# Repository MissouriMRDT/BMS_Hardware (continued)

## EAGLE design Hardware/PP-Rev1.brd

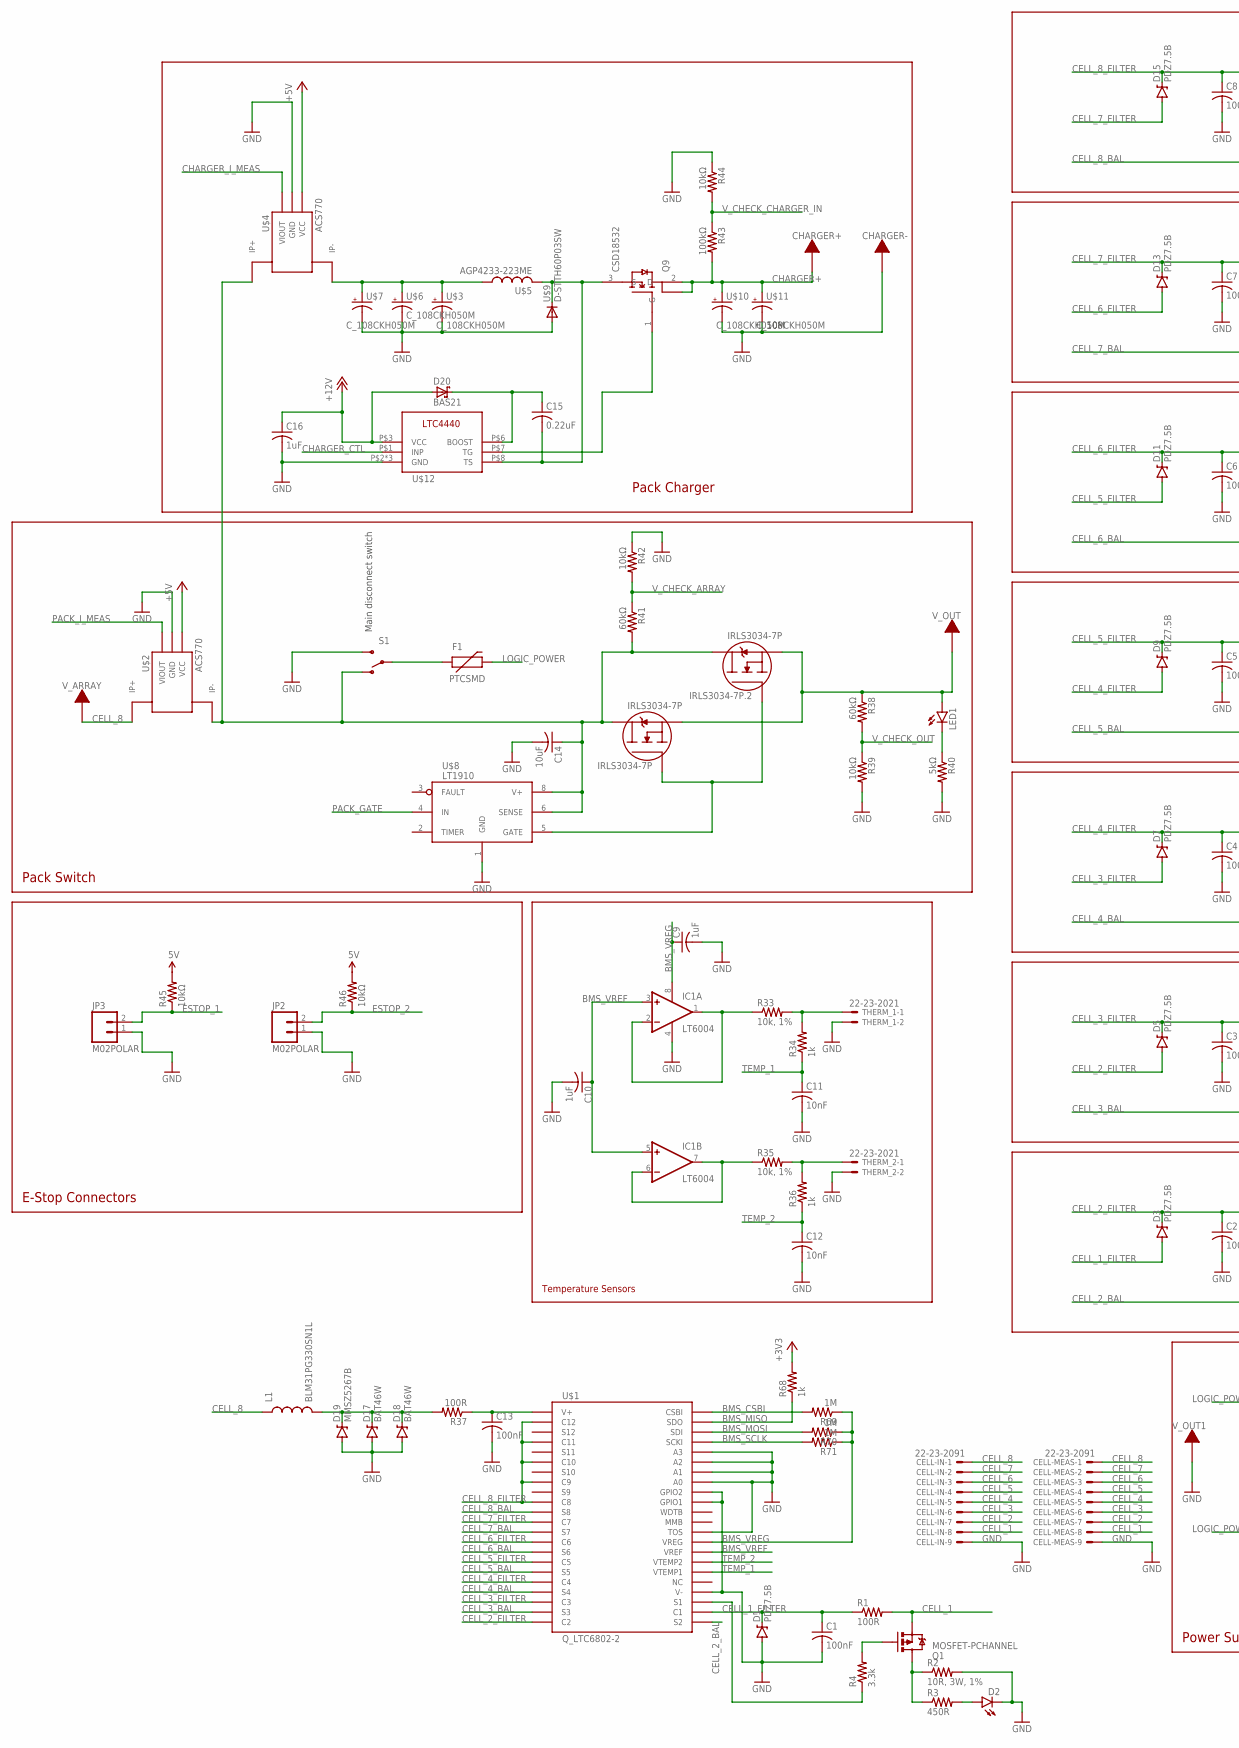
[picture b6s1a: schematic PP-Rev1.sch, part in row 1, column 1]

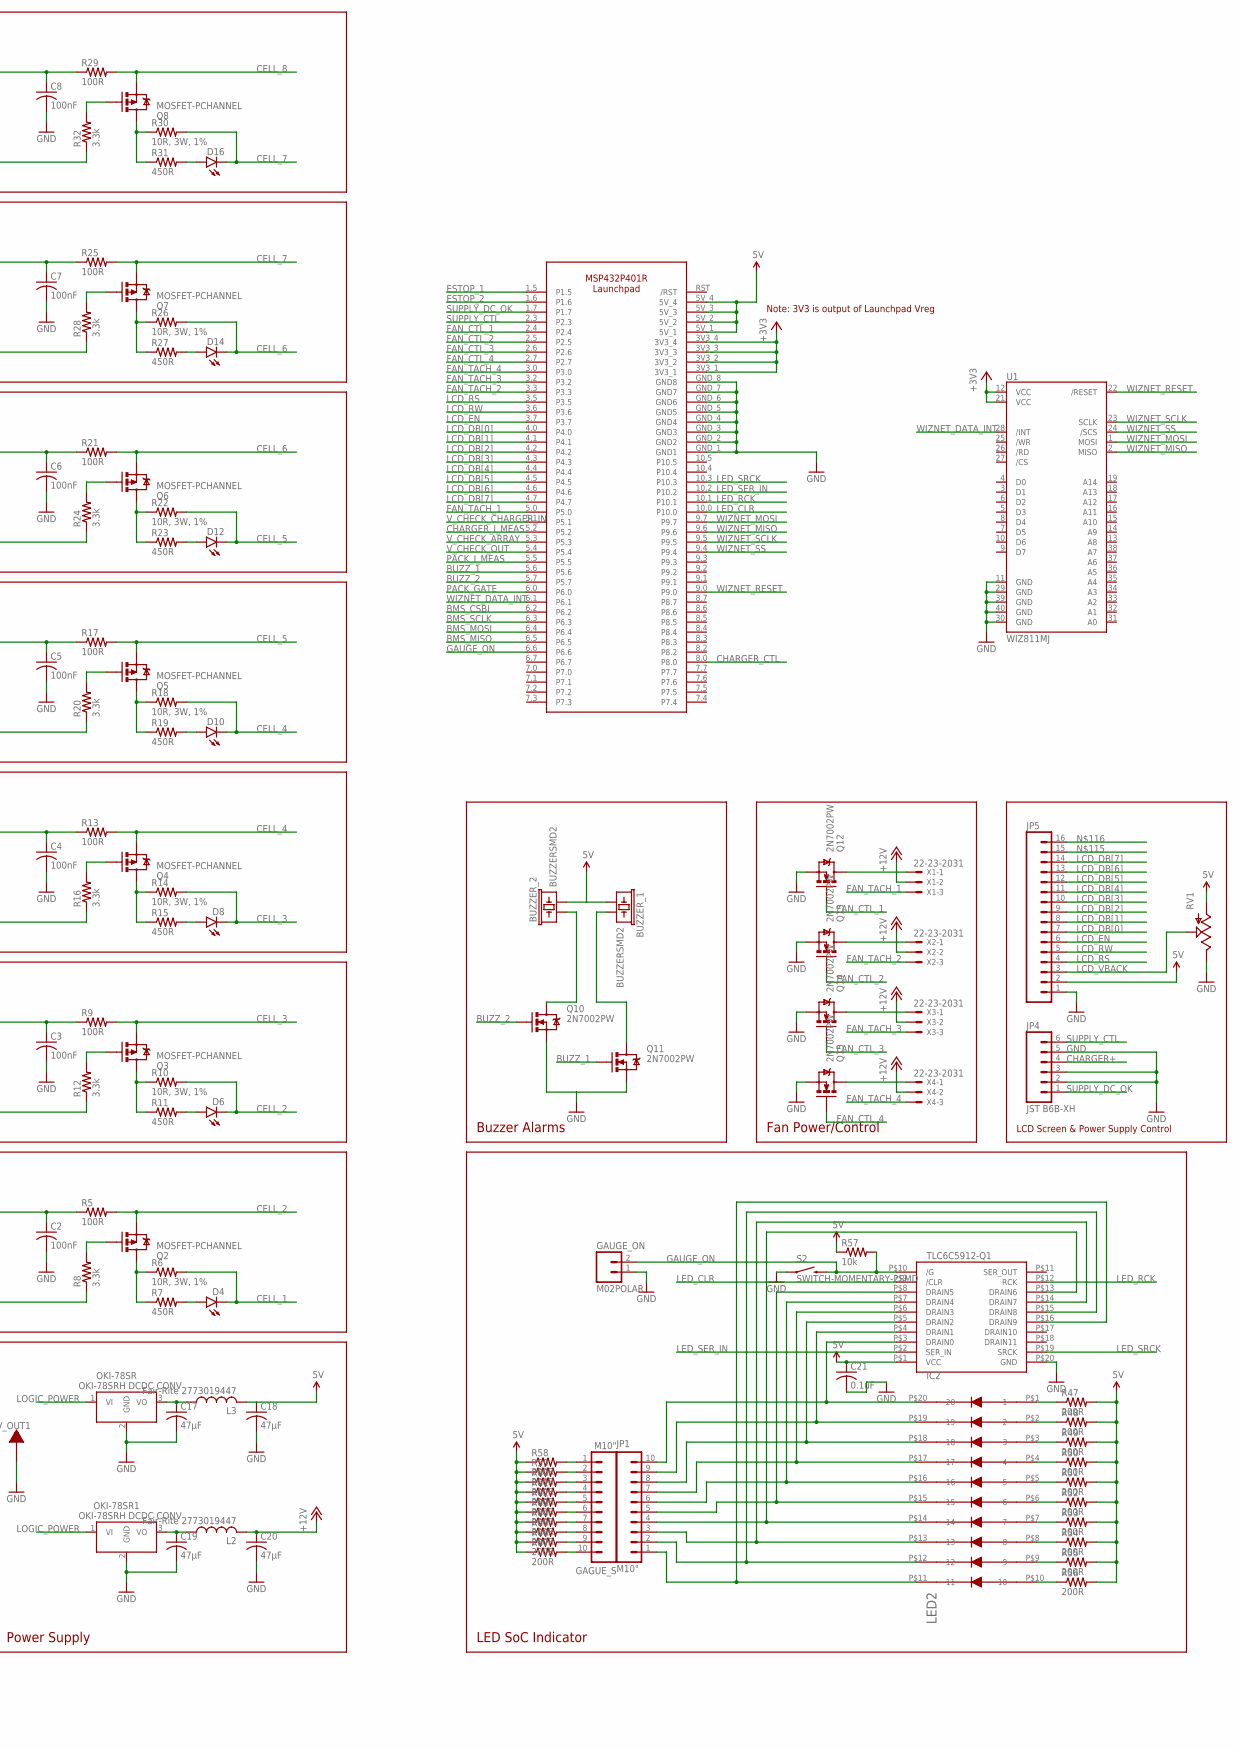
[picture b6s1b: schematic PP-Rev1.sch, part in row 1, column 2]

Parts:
BUZZER_1, BUZZER_2: BUZZERSMD2; BUZZER-CCV
C1, C2, C3, C4, C5, C6, C7, C8, C13: 100nF; C1206
C9, C10, C16: 1uF; C1206
C11, C12: 10nF; C1206
C14: 10uF; C1206
C15: 0.22uF; C1206
C17, C18, C19, C20: 47µF; C1206
C21: 0.1uF; C1206
CELL-IN: 22-23-2091
CELL-MEAS: 22-23-2091
CHARGER+: TERMINAL_HOLE; LARGE_TERMINAL_HOLE
CHARGER-: TERMINAL_HOLE; LARGE_TERMINAL_HOLE
D1, D3, D5, D7, D9, D11, D13, D15: PDZ7.5B; SOD-323
D2, D4, D6, D8, D10, D12, D14, D16: LED1206; LED-1206
D17, D18: BAT46W; SOD-123
D19: MMSZ5267B; SOD-123
D20: BAS21; SOT23
F1: PTCSMD; PTC-1206
GAGUE_S: M10"; 1X10
GAUGE_ON: M02POLAR; MOLEX-1X2
IC1: LT6004; MSOP08
IC2: TLC6C5912-Q1; SOIC-20
IRLS3034-7P, IRLS3034-7P.2: IRLS3034-7P; D2PAK-7
JP1: M10"; 1X10
JP2, JP3: M02POLAR; MOLEX-1X2
JP4: JST B6B-XH; MOLEX-1X6
JP5: M16LONGPADS; 1X16_LONGPADS
L1: BLM31PG330SN1L; 1210
L2, L3: Fair-Rite 2773019447; L8530M
LED1: LED1206; LED-1206
LED2: LED-DC7G3HWA; LED-10
OKI-78SR: Q_OKI-78SR5; OKI-78SRH
OKI-78SR1: Q_OKI-78SR12; OKI-78SRH
Q1, Q2, Q3, Q4, Q5, Q6, Q7, Q8: MOSFET-PCHANNEL; SOT23-3
Q9: CSD18532; TO-220-FLAT
Q10, Q11, Q12, Q13, Q14, Q15: 2N7002PW; SOT323
R1, R5, R9, R13, R17, R21, R25, R29, R37: 100R; R1206
R2, R6, R10, R14, R18, R22, R26, R30: 10R, 3W, 1%; AXIAL-0.6
R3, R7, R11, R15, R19, R23, R27, R31: 450R; 1206
R4, R8, R12, R16, R20, R24, R28, R32: 3.3k; 1206
R33, R35: 10k, 1%; R1206
R34, R36, R68: 1k; R1206
R38, R41: 60kΩ; R1206
R39, R42, R44, R45, R46: 10kΩ; R1206
R40: 5kΩ; R1206
R43: 100kΩ; R1206
R47, R48, R49, R50, R51, R52, R53, R54, R55, R56, R58, R59, R60, R61, R62, R63, R64, R65, R66, R67: 200R; R1206
R57: 10k; R1206
R69, R70, R71: 1M; R1206
RV1: POTTRIM; TRIM_POT
S1: SWITCH-SPDTPTH; SWITCH-SPDT
S2: SWITCH-MOMENTARY-2SMD; TACTILE-SWITCH-SMD
THERM_1, THERM_2: 22-23-2021
U1: WIZ811MJ
U$1: Q_LTC6802-2; SSOP44
U$2, U$4: ACS770; PFF_LEADFORM
U$3, U$6, U$7, U$10, U$11: C_108CKH050M; C_16MM
U$5: AGP4233-223ME; AGP4233
U$8: LT1910; SO8
U$9: D-STTH60P03SW; TO-247-VERT
U$12: LTC4440; MS8E
U$13: MSP432P401R-LAUNCHPAD
V_ARRAY: TERMINAL_HOLE; LARGE_TERMINAL_HOLE
V_OUT, V_OUT1: TERMINAL_HOLE; LARGE_TERMINAL_HOLE
X1, X2, X3, X4: 22-23-2031

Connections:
5V: BUZZER_1.+ (1), BUZZER_2.- (2), C18.1, C21.1, IC2.P$1 (VCC), JP5.2, L3.2, R45.2, R46.2, R47.2, R48.2, R49.2, R50.2, R51.2, R52.2, R53.2, R54.2, R55.2, R56.2, R57.1, R58.1, R59.1, R60.1, R61.1, R62.1, R63.1, R64.1, R65.1, R66.1, R67.1, RV1.3 (A), U$13.5V_1, U$13.5V_2, U$13.5V_3, U$13.5V_4
+3V3: R68.2, U1.12 (VCC), U1.21 (VCC), U$13.3V3_1, U$13.3V3_2, U$13.3V3_3, U$13.3V3_4
+5V: U$2.1 (VCC), U$4.1 (VCC)
+12V: C16.1, C20.1, D20.1 (A), L2.2, U$12.P$3 (VCC), X1.2, X2.2, X3.2, X4.2
BMS_CSBI: R69.2, U$1.44 (CSBI), U$13.6.2
BMS_MISO: R68.1, U$1.43 (SDO), U$13.6.5
BMS_MOSI: R70.2, U$1.42 (SDI), U$13.6.4
BMS_SCLK: R71.2, U$1.41 (SCKI), U$13.6.3
BMS_VREF: C10.1, IC1.3 (+IN), IC1.5 (+IN), U$1.30 (VREF)
BMS_VREG: C9.1, IC1.8 (V+), R69.1, R70.1, R71.1, U$1.31 (VREG)
BUZZ_1: Q11.1 (G), U$13.5.6
BUZZ_2: Q10.1 (G), U$13.5.7
CELL_1: CELL-IN.8, CELL-MEAS.8, D4.C, Q1.2 (S), R1.2, R6.P$2 (2)
CELL_1_BAL: R4.1, U$1.25 (S1)
CELL_1_FILTER: C1.1, D1.C, D3.A, R1.1, U$1.24 (C1)
CELL_2: CELL-IN.7, CELL-MEAS.7, D6.C, Q2.2 (S), R5.2, R10.P$2 (2)
CELL_2_BAL: R8.1, U$1.23 (S2)
CELL_2_FILTER: C2.1, D3.C, D5.A, R5.1, U$1.22 (C2)
CELL_3: CELL-IN.6, CELL-MEAS.6, D8.C, Q3.2 (S), R9.2, R14.P$2 (2)
CELL_3_BAL: R12.1, U$1.21 (S3)
CELL_3_FILTER: C3.1, D5.C, D7.A, R9.1, U$1.20 (C3)
CELL_4: CELL-IN.5, CELL-MEAS.5, D10.C, Q4.2 (S), R13.2, R18.P$2 (2)
CELL_4_BAL: R16.1, U$1.19 (S4)
CELL_4_FILTER: C4.1, D7.C, D9.A, R13.1, U$1.18 (C4)
CELL_5: CELL-IN.4, CELL-MEAS.4, D12.C, Q5.2 (S), R17.2, R22.P$2 (2)
CELL_5_BAL: R20.1, U$1.17 (S5)
CELL_5_FILTER: C5.1, D9.C, D11.A, R17.1, U$1.16 (C5)
CELL_6: CELL-IN.3, CELL-MEAS.3, D14.C, Q6.2 (S), R21.2, R26.P$2 (2)
CELL_6_BAL: R24.1, U$1.15 (S6)
CELL_6_FILTER: C6.1, D11.C, D13.A, R21.1, U$1.14 (C6)
CELL_7: CELL-IN.2, CELL-MEAS.2, D16.C, Q7.2 (S), R25.2, R30.P$2 (2)
CELL_7_BAL: R28.1, U$1.13 (S7)
CELL_7_FILTER: C7.1, D13.C, D15.A, R25.1, U$1.12 (C7)
CELL_8: CELL-IN.1, CELL-MEAS.1, L1.1, Q8.2 (S), R29.2, U$2.4_1 (IP+), U$2.4_2 (IP+), U$2.4_3 (IP+), U$2.4_4 (IP+), U$2.4_5 (IP+), U$2.4_6 (IP+), U$2.4_7 (IP+), U$2.4_8 (IP+), U$2.4_9 (IP+), U$2.4_10 (IP+), U$2.4_11 (IP+), U$2.4_12 (IP+), U$2.4_13 (IP+), U$2.4_14 (IP+), U$2.4_15 (IP+), U$2.4_16 (IP+), U$2.4_B (IP+), U$2.4_T (IP+), V_ARRAY.P$1
CELL_8_BAL: R32.1, U$1.11 (S8)
CELL_8_FILTER: C8.1, D15.C, R29.1, U$1.2 (C12), U$1.4 (C11), U$1.6 (C10), U$1.8 (C9), U$1.10 (C8)
CHARGER+: CHARGER+.P$1, JP4.4, Q9.2 (D), Q9.4, R43.2, U$10.+, U$11.+
CHARGER_CTL: U$12.P$1 (INP), U$13.8.0
CHARGER_I_MEAS: U$4.3 (VIOUT), U$13.5.2
ESTOP_1: JP3.2, R45.1, U$13.1.5
ESTOP_2: JP2.2, R46.1, U$13.1.6
FAN_CTL_1: Q12.1 (G), U$13.2.4
FAN_CTL_2: Q13.1 (G), U$13.2.5
FAN_CTL_3: Q14.1 (G), U$13.2.6
FAN_CTL_4: Q15.1 (G), U$13.2.7
FAN_TACH_1: U$13.5.0, X1.3
FAN_TACH_2: U$13.3.3, X2.3
FAN_TACH_3: U$13.3.2, X3.3
FAN_TACH_4: U$13.3.0, X4.3
GAUGE_D: IC2.P$6 (DRAIN3), JP1.7, LED2.P$17 (17)
GAUGE_ON: GAUGE_ON.2, IC2.P$10 (/G), R57.2, S2.3 (2), U$13.6.6
GND: C1.2, C2.2, C3.2, C4.2, C5.2, C6.2, C7.2, C8.2, C9.2, C10.2, C11.2, C12.2, C13.2, C14.2, C16.2, C17.2, C18.2, C19.2, C20.2, C21.2, CELL-IN.9, CELL-MEAS.9, CHARGER-.P$1, D1.A, D2.C, D17.A, D18.A, D19.A, GAUGE_ON.1, IC1.4 (V-), IC2.P$20 (GND), JP2.1, JP3.1, JP4.2, JP4.3, JP4.5, JP5.1, OKI-78SR.2 (GND), OKI-78SR1.2 (GND), Q10.2 (S), Q11.2 (S), Q12.2 (S), Q13.2 (S), Q14.2 (S), Q15.2 (S), R2.P$2 (2), R39.2, R40.2, R42.1, R44.1, RV1.2 (E), S1.3 (S), S2.1, THERM_1.2, THERM_2.2, U1.11 (GND), U1.29 (GND), U1.30 (GND), U1.39 (GND), U1.40 (GND), U$1.26 (V-), U$1.32 (TOS), U$1.35 (GPIO1), U$1.36 (GPIO2), U$1.37 (A0), U$1.38 (A1), U$1.39 (A2), U$1.40 (A3), U$2.2 (GND), U$3.GND (-), U$4.2 (GND), U$6.GND (-), U$7.GND (-), U$8.1 (GND), U$9.P$1 (A), U$9.P$3 (A), U$10.GND (-), U$11.GND (-), U$12.P$2 (GND), U$12.P$4 (GND), U$12.P$9 (GND), U$13.GND_1 (GND1), U$13.GND_2 (GND2), U$13.GND_3 (GND3), U$13.GND_4 (GND4), U$13.GND_5 (GND5), U$13.GND_6 (GND6), U$13.GND_7 (GND7), U$13.GND_8 (GND8), V_OUT1.P$1
LCD_DB[0]: JP5.7, U$13.4.0
LCD_DB[1]: JP5.8, U$13.4.1
LCD_DB[2]: JP5.9, U$13.4.2
LCD_DB[3]: JP5.10, U$13.4.3
LCD_DB[4]: JP5.11, U$13.4.4
LCD_DB[5]: JP5.12, U$13.4.5
LCD_DB[6]: JP5.13, U$13.4.6
LCD_DB[7]: JP5.14, U$13.4.7
LCD_EN: JP5.6, U$13.3.7
LCD_RS: JP5.4, U$13.3.5
LCD_RW: JP5.5, U$13.3.6
LCD_VBACK: JP5.3, RV1.1 (S)
LED_CLR: IC2.P$9 (/CLR), U$13.10.0
LED_RCK: IC2.P$12 (RCK), U$13.10.1
LED_SER_IN: IC2.P$2 (SER_IN), U$13.10.2
LED_SRCK: IC2.P$19 (SRCK), U$13.10.3
LOGIC_POWER: F1.2, OKI-78SR.1 (VI), OKI-78SR1.1 (VI)
unnamed: Q3.3 (D), R10.P$1 (1), R11.1
unnamed: Q1.3 (D), R2.P$1 (1), R3.1
unnamed: D2.A, R3.2
unnamed: D6.A, R11.2
unnamed: Q1.1 (G), R4.2
unnamed: Q3.1 (G), R12.2
unnamed: Q2.3 (D), R6.P$1 (1), R7.1
unnamed: D4.A, R7.2
unnamed: Q2.1 (G), R8.2
unnamed: Q4.3 (D), R14.P$1 (1), R15.1
unnamed: D8.A, R15.2
unnamed: Q4.1 (G), R16.2
unnamed: Q5.3 (D), R18.P$1 (1), R19.1
unnamed: D10.A, R19.2
unnamed: Q5.1 (G), R20.2
unnamed: Q6.3 (D), R22.P$1 (1), R23.1
unnamed: D12.A, R23.2
unnamed: Q6.1 (G), R24.2
unnamed: Q7.3 (D), R26.P$1 (1), R27.1
unnamed: D14.A, R27.2
unnamed: Q7.1 (G), R28.2
unnamed: Q8.3 (D), R30.P$1 (1), R31.1
unnamed: D16.A, R31.2
unnamed: Q8.1 (G), R32.2
unnamed: IC1.1 (OUT), IC1.2 (-IN), R33.1
unnamed: D17.C, D18.C, D19.C, L1.2, R37.2
unnamed: IC1.6 (-IN), IC1.7 (OUT), R35.1
unnamed: U$3.+, U$4.5_1 (IP-), U$4.5_2 (IP-), U$4.5_3 (IP-), U$4.5_4 (IP-), U$4.5_5 (IP-), U$4.5_6 (IP-), U$4.5_7 (IP-), U$4.5_8 (IP-), U$4.5_9 (IP-), U$4.5_10 (IP-), U$4.5_11 (IP-), U$4.5_12 (IP-), U$4.5_13 (IP-), U$4.5_14 (IP-), U$4.5_15 (IP-), U$4.5_16 (IP-), U$4.5_B (IP-), U$4.5_T (IP-), U$5.P$1 (1), U$6.+, U$7.+
unnamed: R33.2, R34.2, THERM_1.1
unnamed: R35.2, R36.2, THERM_2.1
unnamed: C13.1, R37.1, U$1.1 (V+)
unnamed: IC2.P$3 (DRAIN0), JP1.10, LED2.P$20 (20)
unnamed: C19.1, L2.1, OKI-78SR1.3 (VO)
unnamed: IRLS3034-7P.1 (GATE), IRLS3034-7P.2.1 (GATE), U$8.5 (GATE)
unnamed: LED1.C, R40.1
unnamed: IRLS3034-7P.2 (SOURCE), IRLS3034-7P.3 (SOURCE), IRLS3034-7P.4 (SOURCE), IRLS3034-7P.5 (SOURCE), IRLS3034-7P.6 (SOURCE), IRLS3034-7P.2.2 (SOURCE), IRLS3034-7P.2.3 (SOURCE), IRLS3034-7P.2.4 (SOURCE), IRLS3034-7P.2.5 (SOURCE), IRLS3034-7P.2.6 (SOURCE), LED1.A, R38.1, V_OUT.P$1
unnamed: C15.1, D20.3 (C), U$12.P$6 (BOOST)
unnamed: C15.2, Q9.3 (S), U$5.P$2 (2), U$9.P$2 (C), U$12.P$8 (TS)
unnamed: Q9.1 (G), U$12.P$7 (TG)
unnamed: C14.1, IRLS3034-7P.PAD (DRAIN), IRLS3034-7P.2.PAD (DRAIN), R41.2, S1.1 (O), U$2.5_1 (IP-), U$2.5_2 (IP-), U$2.5_3 (IP-), U$2.5_4 (IP-), U$2.5_5 (IP-), U$2.5_6 (IP-), U$2.5_7 (IP-), U$2.5_8 (IP-), U$2.5_9 (IP-), U$2.5_10 (IP-), U$2.5_11 (IP-), U$2.5_12 (IP-), U$2.5_13 (IP-), U$2.5_14 (IP-), U$2.5_15 (IP-), U$2.5_16 (IP-), U$2.5_B (IP-), U$2.5_T (IP-), U$4.4_1 (IP+), U$4.4_2 (IP+), U$4.4_3 (IP+), U$4.4_4 (IP+), U$4.4_5 (IP+), U$4.4_6 (IP+), U$4.4_7 (IP+), U$4.4_8 (IP+), U$4.4_9 (IP+), U$4.4_10 (IP+), U$4.4_11 (IP+), U$4.4_12 (IP+), U$4.4_13 (IP+), U$4.4_14 (IP+), U$4.4_15 (IP+), U$4.4_16 (IP+), U$4.4_B (IP+), U$4.4_T (IP+), U$8.6 (SENSE), U$8.8 (V+)
unnamed: F1.1, S1.2
unnamed: IC2.P$4 (DRAIN1), JP1.9, LED2.P$19 (19)
unnamed: IC2.P$5 (DRAIN2), JP1.8, LED2.P$18 (18)
unnamed: IC2.P$7 (DRAIN4), JP1.6, LED2.P$16 (16)
unnamed: IC2.P$8 (DRAIN5), JP1.5, LED2.P$15 (15)
unnamed: IC2.P$13 (DRAIN6), JP1.4, LED2.P$14 (14)
unnamed: IC2.P$14 (DRAIN7), JP1.3, LED2.P$13 (13)
unnamed: IC2.P$15 (DRAIN8), JP1.2, LED2.P$12 (12)
unnamed: IC2.P$16 (DRAIN9), JP1.1, LED2.P$11 (11)
unnamed: LED2.P$1 (1), R47.1
unnamed: LED2.P$2 (2), R48.1
unnamed: LED2.P$3 (3), R49.1
unnamed: LED2.P$4 (4), R50.1
unnamed: LED2.P$5 (5), R51.1
unnamed: LED2.P$6 (6), R52.1
unnamed: LED2.P$7 (7), R53.1
unnamed: LED2.P$8 (8), R54.1
unnamed: LED2.P$9 (9), R55.1
unnamed: LED2.P$10 (10), R56.1
unnamed: BUZZER_1.- (2), Q11.3 (D)
unnamed: BUZZER_2.+ (1), Q10.3 (D)
unnamed: Q12.3 (D), X1.1
unnamed: Q13.3 (D), X2.1
unnamed: Q14.3 (D), X3.1
unnamed: Q15.3 (D), X4.1
unnamed: GAGUE_S.1, R58.2
unnamed: GAGUE_S.2, R59.2
unnamed: GAGUE_S.3, R60.2
unnamed: GAGUE_S.4, R61.2
unnamed: GAGUE_S.5, R62.2
unnamed: GAGUE_S.6, R63.2
unnamed: GAGUE_S.7, R64.2
unnamed: GAGUE_S.8, R65.2
unnamed: GAGUE_S.9, R66.2
unnamed: GAGUE_S.10, R67.2
unnamed: C17.1, L3.1, OKI-78SR.3 (VO)
PACK_GATE: U$8.4 (IN), U$13.6.0
PACK_I_MEAS: U$2.3 (VIOUT), U$13.5.5
SUPPLY_CTL: JP4.6, U$13.2.3
SUPPLY_DC_OK: JP4.1, U$13.1.7
TEMP_1: C11.1, R34.1, U$1.28 (VTEMP1)
TEMP_2: C12.1, R36.1, U$1.29 (VTEMP2)
V_CHECK_ARRAY: R41.1, R42.2, U$13.5.3
V_CHECK_CHARGER_IN: R43.1, R44.2, U$13.5.1
V_CHECK_OUT: R38.2, R39.1, U$13.5.4
WIZNET_DATA_INT: U1.28 (/INT), U$13.6.1
WIZNET_MISO: U1.2 (MISO), U$13.9.6
WIZNET_MOSI: U1.1 (MOSI), U$13.9.7
WIZNET_RESET: U1.22 (/RESET), U$13.9.0
WIZNET_SCLK: U1.23 (SCLK), U$13.9.5
WIZNET_SS: U1.24 (/SCS), U$13.9.4

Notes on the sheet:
Temperature Sensors
Pack Switch
Pack Charger
Main disconnect switch
E-Stop Connectors
Power Supply
LED SoC Indicator
Buzzer Alarms
Fan Power/Control
LCD Screen & Power Supply Control
Note: 3V3 is output of Launchpad Vreg

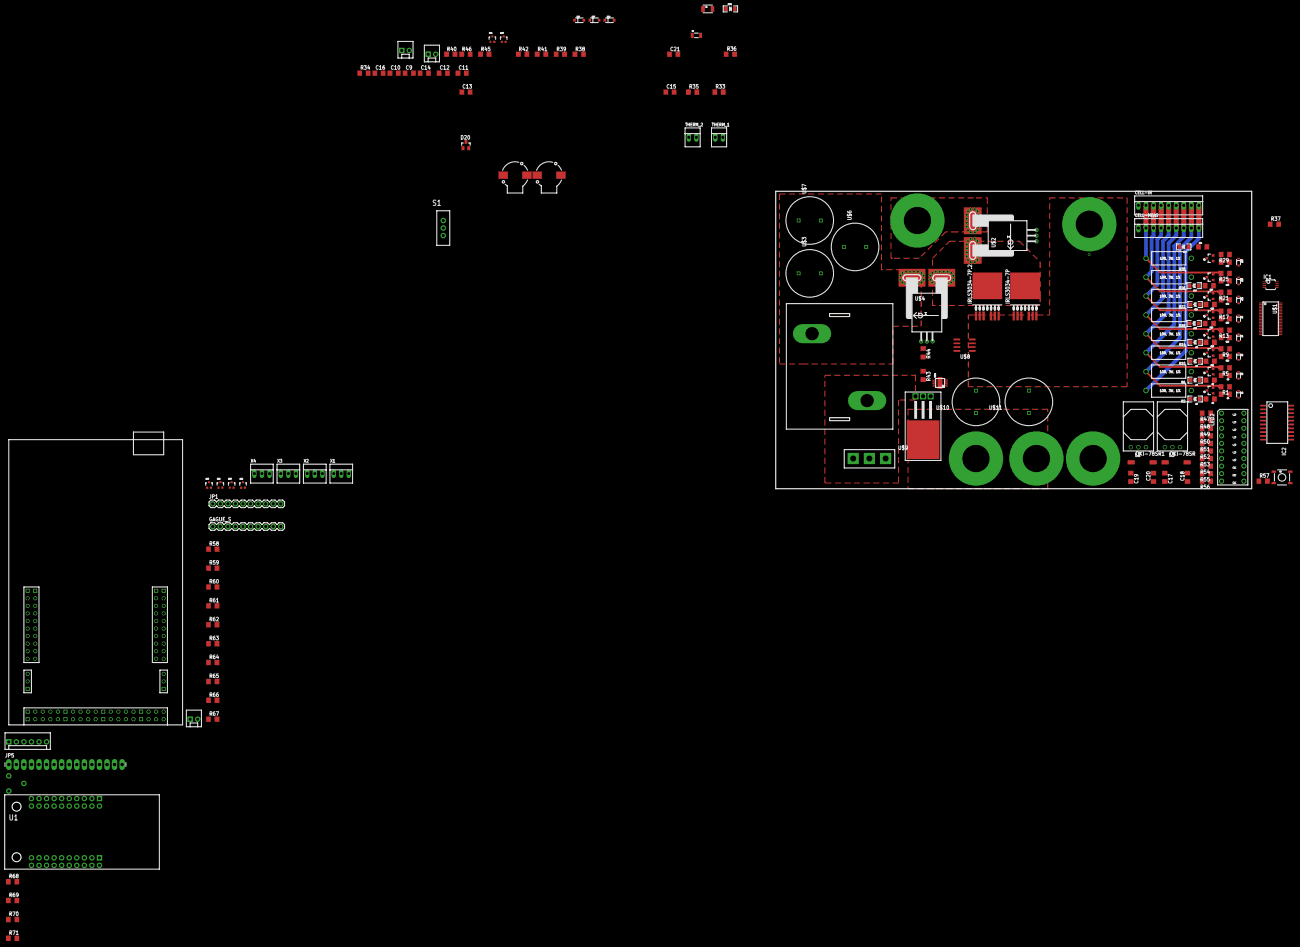
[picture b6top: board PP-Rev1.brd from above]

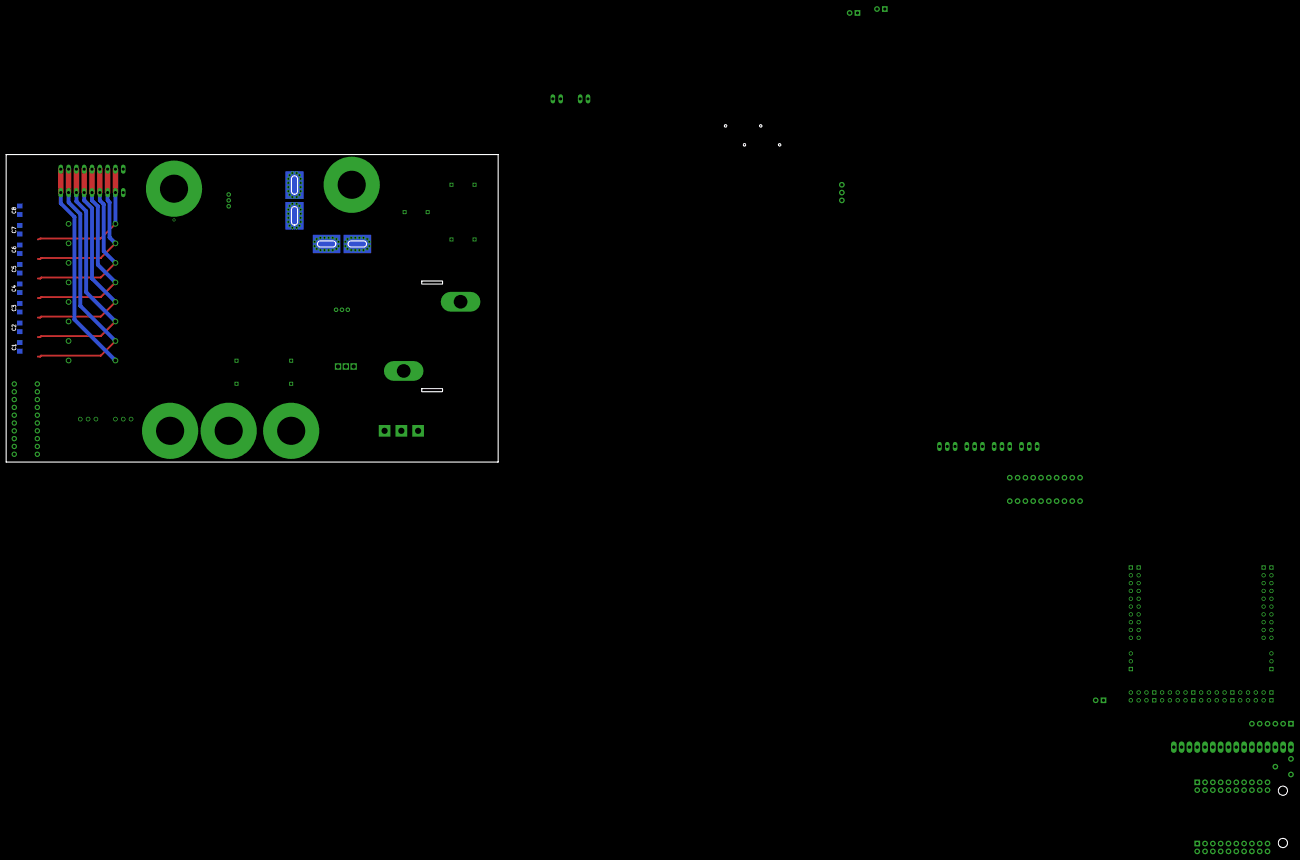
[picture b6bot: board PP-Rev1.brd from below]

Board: 2 copper layers, 160.0 x 100.0 mm, 178 parts (8 on the bottom side), 160 nets.

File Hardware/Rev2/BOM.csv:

"Qty";"Value";"Device";"Package";"Parts";"Description";"MF";"MPN";"OC_FARNELL";"OC_NEWARK";"PROD_ID";"VALUE";
"2";"";"IRLS3034-7P";"D2PAK-7";"IRLS3034-7P, IRLS3034-7P.2";"High-current SMD MOSFET";"";"";"";"";"";"";
"9";"";"LED1206";"LED-1206";"D2, D4, D6, D8, D10, D12, D14, D16, LED1";"LEDs";"";"";"";"";"";"";
"1";"";"M16LONGPADS";"1X16_LONGPADS";"JP5";"1x16 .1" header";"";"";"";"";"";"";
"1";"";"POTTRIM";"TRIM_POT";"RV1";"";"";"";"";"";"";"";
"1";"";"SWITCH-SPDTPTH";"SWITCH-SPDT";"S1";"SPDT Switch";"";"";"";"";"";"";
"1";"0.1uF";"C-USC1206";"C1206";"C21";"CAPACITOR, American symbol";"";"";"";"";"";"";
"1";"0.22uF";"C-USC1206";"C1206";"C15";"CAPACITOR, American symbol";"";"";"";"";"";"";
"9";"100R";"R-US_R1206";"R1206";"R1, R5, R9, R13, R17, R21, R25, R29, R37";"RESISTOR, American symbol";"";"";"";"";"";"";
"1";"100kΩ";"R-US_R1206";"R1206";"R43";"RESISTOR, American symbol";"";"";"";"";"";"";
"9";"100nF";"C-USC1206";"C1206";"C1, C2, C3, C4, C5, C6, C7, C8, C13";"CAPACITOR, American symbol";"";"";"";"";"";"";
"8";"10R, 3W, 1%";"RESISTORPTH-1W";"AXIAL-0.6";"R2, R6, R10, R14, R18, R22, R26, R30";"Resistor";"";"";"";"";"";"";
"1";"10k";"R-US_R1206";"R1206";"R57";"RESISTOR, American symbol";"";"";"";"";"";"";
"2";"10k, 1%";"R-US_R1206";"R1206";"R33, R35";"RESISTOR, American symbol";"";"";"";"";"";"";
"5";"10kΩ";"R-US_R1206";"R1206";"R39, R42, R44, R45, R46";"RESISTOR, American symbol";"";"";"";"";"";"";
"2";"10nF";"C-USC1206";"C1206";"C11, C12";"CAPACITOR, American symbol";"";"";"";"";"";"";
"1";"10uF";"C-USC1206";"C1206";"C14";"CAPACITOR, American symbol";"";"";"";"";"";"";
"2";"120 Ohm";"RESISTOR1206";"1206";"R72, R73";"Resistor";"";"";"";"";"";"";
"3";"1M";"R-US_R1206";"R1206";"R69, R70, R71";"RESISTOR, American symbol";"";"";"";"";"";"";
"3";"1k";"R-US_R1206";"R1206";"R34, R36, R68";"RESISTOR, American symbol";"";"";"";"";"";"";
"4";"1uF";"C-USC1206";"C1206";"C9, C10, C16, C22";"CAPACITOR, American symbol";"";"";"";"";"";"";
"20";"200R";"R-US_R1206";"R1206";"R47, R48, R49, R50, R51, R52, R53, R54, R55, R56, R58, R59, R60, R61, R62, R63, R64, R65, R66, R67";"RESISTOR, American symbol";"";"";"";"";"";"";
"2";"22-23-2021";"22-23-2021";"22-23-2021";"THERM_1, THERM_2";".100" (2.54mm) Center Header - 2 Pin";"MOLEX";"22-23-2021";"1462926";"25C3832";"";"";
"4";"22-23-2031";"22-23-2031";"22-23-2031";"X1, X2, X3, X4";".100" (2.54mm) Center Header - 3 Pin";"MOLEX";"22-23-2031";"1462950";"30C0862";"";"";
"2";"22-23-2091";"22-23-2091";"22-23-2091";"CELL-IN, CELL-MEAS";".100" (2.54mm) Center Header - 9 Pin";"MOLEX";"22-23-2091";"1756827";"56H0450";"";"";
"6";"2N7002PW";"MOSFET-NCHANNEL2N7002PW";"SOT323";"Q10, Q11, Q12, Q13, Q14, Q15";"Common NMOSFET Parts";"";"";"";"";"TRANS-11151";"";
"8";"3.3k";"RESISTOR1206";"1206";"R4, R8, R12, R16, R20, R24, R28, R32";"Resistor";"";"";"";"";"";"";
"8";"450R";"RESISTOR1206";"1206";"R3, R7, R11, R15, R19, R23, R27, R31";"Resistor";"";"";"";"";"";"";
"4";"47µF";"C-USC1206";"C1206";"C17, C18, C19, C20";"CAPACITOR, American symbol";"";"";"";"";"";"";
"1";"5kΩ";"R-US_R1206";"R1206";"R40";"RESISTOR, American symbol";"";"";"";"";"";"";
"2";"60kΩ";"R-US_R1206";"R1206";"R38, R41";"RESISTOR, American symbol";"";"";"";"";"";"";
"2";"ACS770";"ACS770";"PFF_LEADFORM";"U$2, U$4";"";"";"";"";"";"";"";
"1";"AGP4233-223ME";"AGP4233";"AGP4233";"U$5";"";"";"";"";"";"";"";
"1";"BAS21";"BAS40";"SOT23";"D20";"Silicon Schottky Diodes";"";"";"";"";"";"";
"2";"BAT46W";"DIODE-ZENER16V";"SOD-123";"D17, D18";"Zener Diode";"";"";"";"";"DIO-12440";"16V";
"1";"BLM31PG330SN1L";"INDUCTOR1210";"1210";"L1";"Inductors";"";"";"";"";"";"";
"2";"BUZZERSMD2";"BUZZERSMD2";"BUZZER-CCV";"BUZZER_1, BUZZER_2";"Buzzer 12mm";"";"";"";"";"";"";
"1";"CSD18532";"Q_CSD18532KCSPCB";"TO-220-FLAT";"Q9";"60V 100A N Channel MOSFET";"";"";"";"";"";"";
"5";"C_108CKH050M";"C_108CKH050M";"C_16MM";"U$3, U$6, U$7, U$10, U$11";"CAP ALUM 50V 0.1mF 1.1A ripple";"";"";"";"";"";"";
"1";"D-STTH60P03SW";"D-STTH60P03SW";"TO-247-VERT";"U$9";"";"";"";"";"";"";"";
"2";"Fair-Rite 2773019447";"L-USL8530M";"L8530M";"L2, L3";"INDUCTOR, American symbol";"";"";"";"";"";"";
"1";"JST B6B-XH";"M06POLAR";"MOLEX-1X6";"JP4";"Header 6";"";"";"";"";"";"";
"1";"J_0399700102";"J_0399700102";"J_2CONHC";"J1";"High Current Power Connector";"";"";"";"";"";"";
"1";"LED-DC7G3HWA";"LED-DC7G3HWA";"LED-10";"LED2";"10 segement LED - Kingbright part # DC7G3HWA";"";"";"";"";"";"";
"1";"LT1910";"LT1910";"SO8";"U$8";"";"";"";"";"";"";"";
"1";"LT6004";"OPA2345E";"MSOP08";"IC1";"Dual Operational Amplifier";"";"";"";"";"";"";
"1";"LTC4440";"LTC4440";"MS8E";"U$12";"";"";"";"";"";"";"";
"3";"M02POLAR";"M02POLAR";"MOLEX-1X2";"GAUGE_ON, JP2, JP3";"Standard 2-pin 0.1" header. Use with";"";"";"";"";"";"";
"2";"M10"";"M10"";"1X10";"GAGUE_S, JP1";"Header 10";"";"";"";"";"";"";
"1";"MAX3077";"MAX3077";"MAX3070E";"U$15";"";"";"";"";"";"";"";
"1";"MMSZ5267B";"DIODE-ZENER16V";"SOD-123";"D19";"Zener Diode";"";"";"";"";"DIO-12440";"16V";
"8";"MOSFET-PCHANNEL";"MOSFET-PCHANNEL";"SOT23-3";"Q1, Q2, Q3, Q4, Q5, Q6, Q7, Q8";"Generic PMOSFET";"";"";"";"";"TRANS-08285";"";
"1";"MSP432P401R-LAUNCHPAD";"MSP432P401R-LAUNCHPAD";"MSP432P401R-LAUNCHPAD";"U$13";"";"";"";"";"";"";"";
"8";"PDZ7.5B";"DIODE-ZENER5.6V";"SOD-323";"D1, D3, D5, D7, D9, D11, D13, D15";"Zener Diode";"";"";"";"";"DIO-12442";"5.6V";
"1";"PTCSMD";"PTCSMD";"PTC-1206";"F1";"Resettable Fuse PTC";"";"";"";"";"RES-11150";"";
"1";"Q_LTC6802-2";"Q_LTC6802-2";"SSOP44";"U$1";"";"";"";"";"";"";"";
"1";"Q_OKI-78SR12";"Q_OKI-78SR";"OKI-78SRH";"OKI-78SR1";"4.95W DC/DC Converter";"";"";"";"";"";"";
"1";"Q_OKI-78SR5";"Q_OKI-78SR";"OKI-78SRH";"OKI-78SR";"4.95W DC/DC Converter";"";"";"";"";"";"";
"1";"RJ45-8PTH";"RJ45-8PTH";"RJ45-8";"U$14";"RJ45 Jack";"";"";"";"";"";"";
"1";"SWITCH-MOMENTARY-2SMD";"SWITCH-MOMENTARY-2SMD";"TACTILE-SWITCH-SMD";"S2";"Various NO switches- pushbuttons, reed, etc";"";"";"";"";"SWCH-08247";"";
"3";"TERMINAL_HOLE";"TERMINAL_HOLE";"LARGE_TERMINAL_HOLE";"V_ARRAY, V_OUT, V_OUT1";"";"";"";"";"";"";"";
"1";"TLC6C5912-Q1";"TLC6C5912-Q1";"SOIC-20";"IC2";"";"";"";"";"";"";"";

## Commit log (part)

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2020-10-08 TIVA added, current sense WIP
    started the current sense circuit. added the tiva layout, need to ask if there is a better way
2020-10-09 changed layout
2020-10-11 did some wiring n stuff
2020-10-13 buzzer started, 5v buck needs R values
2020-10-15 idk what changed
2020-10-17 no connects added
2020-10-31 stuff added
    -cellFilter IC and R values added
    -MOSFET values added
    -extra TIVA headers added
    -currentSense R values labeled properly
    -things are actually connected together this time
2020-11-03 annotated sch.
    some ICs got moved around- solve later
2020-11-03 more footprints added
2020-11-09 50mOhm R footprint edited, Conn2 pad 2 set to V_in
    May need to reconnect Conn2 to V_in each time a new net list is generated
2020-11-09 Tiva footprint moved, began positioning estop
    Need to finish estop circuit,
    moved vias slightly to fit tiva headers
2020-11-10 Q2,3 footprint updated, via stitched V_in, TIVA moved
    -need to update schematic symbols Q2,3
    -double check TIVA orientation
2020-11-14 moved hierarchical sheets into their own filter and cleaned up Hardware folder
2020-11-14 moved symbols into dedicated Documentation/Libraries/Symbols folder
2020-11-14 switched mosfet symbol to new one
2020-11-14 re-oriented lt1910 (was backwards) and continued layout
    ESTOP layout done, cellFilters in progress
2020-11-15 cellFilter 1 connected to connector
2020-11-15 more circuits built, tiva and cell filter repositioned to allow space for gnd via
2020-11-15 cellFilters done (including i-sense lines)
2020-11-15 cellFilter reajusted (per Alisa reqest), started 3v3 buck layout
2020-11-15 cellFilter done, rewired estop circuit
2020-11-16 GND vias added, ind moved into positions
2020-11-16 IND added, began GND stitching around cellFilters
2020-11-16 did more gnd planing
2020-11-17 got new board dimentions, moved right side vias into position, TODO: fix stuff around it
2020-11-21 battConn moved, LCD conn added into position, top left mounting hole added
2020-11-21 bucks moved, need to replace w okis
2020-11-22 replaced bucks w okis in schematic, generated netlist
2020-11-22 ADDED silkscreens folder
2020-11-22 gnd stitching done
2020-11-22 did some stitching, done for the day.
    ToDo: Fix cellFiltering by moving the schot. diodes and filtering caps towards connector and the zener diodes to the tiva
2020-11-23 Fixed cellFilter schematic by moving diodes btwn cells, generated new netlist
2020-11-23 Connected cell inputs for cellFilter 1 (need to hook up to tiva and work on ic 2)
2020-11-24 Revert "continued wiring the cellFilters. cells 1-7 are now done (working on improvements)"
    This reverts commit 30bd659c1e722bf1891392f90f37f2d2aea567cf.
2020-11-24 cellFilter arrangement done, Caps and schot. diodes rearranged to have better gnding
2020-11-24 cellFilter ICs give power
2020-11-24 had forgot to add in cellFIlter Caps, added it (and kept the circuit well-grounded)
2020-11-24 reinforce gnding around charging port
2020-11-24 routed 3v3 to top of board, added more diodes.
2020-11-24 rerouted 6,7,8 to get better gnding around cell lines
2020-11-25 added fuse plane, more vias to V_in and V_out
2020-11-25 worked on BOM (also got approval for layout!)
2020-11-25 needed to change R45,R40 ( and the associated other resistor values) to something in stock
    Instead of an exact 3.3 V output, now there is 3.287
2020-11-25 BOM finished
2020-11-27 moved vias off of small pads of cellFilter IC 1
2020-11-27 made gnding on back plane more solid but moving traces to front
    Also changed the clearence on the planes to 10 (from 20)
    also rotated the mrdt logo on b silk
2020-11-27 moved BOM to DOCUMENTATION FOLDER
2020-11-27 generated new Gerbs
2020-11-28 new gerbs generated
2020-12-05 added dimentions, next changes will be a rev 2
2021-01-12 moved OKIs closer to each other, added logic_power plane, currently redrawing power traces to make room for PV plane extension
2021-01-16 test commit, moved irrelevent schot. diode silkscreens
2021-01-20 added qr silkscreen, moved estop and ONOFF button connectors, currently rewiring
2021-01-20 redrew traces from btwn PV and V_out planes (more efficient) and improved GNDing. switched ESTOP and ONOFF conn placement.
2021-01-20 traced MST
2021-03-11 Added TIVA footprint, generated new netlist
    In the process of changing schott. diodes to bigger footprints.
    Most likely going to reorganize components on the board
2021-03-12 cell filters 1-4 constructed
2021-03-12 new schott. diodes added in layout
    ToDo: Finished connecting LEDS and various things that need +5V and +3V3
2021-03-12 moving LCD and Temp connectors to allow for better mounting
    may revert back to previous commit, undecided.
2021-03-12 qrcode added
2021-03-18 New BOM generated
    BOM in .xlsx format
2021-04-02 replaced cellFilter ICs with last gen chip
    Replaced with the chipset alisa used because they are more reliable and work better based off of bench testing of my chip.
2021-04-02 CF one trace away from complete.
    Still need to ground better in some areas.
2021-10-03 Created hierarchy sheets
    Added Tiva and the hierarchy sheets for each circuit
2021-10-03 Undoing Changes to Master
2021-10-05 Removed Autosaved Rescue Library
    Removed Rescue Library because of Github push issues
2021-10-06 Created the power input, power output, and current measurement schematic
    Added Labels and defined Resistances and Capacitance for components
2021-10-09 Added the labels to the Tiva and created the Temperature Sensor
    The Tiva global labels were added and the voltage monitoring schematic and the temperature schematic were created.
2021-10-09 Created a 9V battery connection circuit to oki
    Created a 9v connection circuit to oki to connect to the cell filter circuit at 5V and the 5V of the tiva
2021-10-16 Placed in new Op Amps and 9V battery to power Tiva
    Placed in new Op Amps and 9V battery
2021-10-17 double check the annotations
    adjusted some field value
2021-10-20 Downloaded Schematic
    Downloaded Schematic PDF for documentation of BMS building
2021-11-05 reworking 3-way networkswitch
    Remapping 3-way network switch for logic simplification and power flow to mosfet
2021-11-13 Replaced Differential Op-Amp because of Chip Shortage
    Replace Differential Op-Amp because of chip shortage and replaced the schematic layout of Cell Monitor with the Generic Differential Op-Amp layout with matching resistor and diode values of the Diffe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
2021-11-13 Replaced SL Molex connectors with Microfit Molex connectors
    Replaced SL Molex connectors with Micro fit Molex connectors because Micro fit is more structurally sound
2021-11-16 Changed the TIVA to a Teensy
    The Tiva was changed to a Teensy for size management of the BMS board. The Teensy is significantly smaller and weighs less while still having the same functionality of the Tiva.
2021-11-18 Created PCB still need to finish making the rest of the connections to the Teensy
    Need to finish making connections of the Teensy to components on the board for power and communication for the individual components
2021-11-27 Reworking BMS Traces and overall layout
    Removed BMS Traces and components to re-organize and to properly place the correct traces and power planes on BMS to meet BMS requirements
2021-11-30 layout design update: symbol placement (unwired)
2021-11-30 updated schematic design for better layout
2021-12-01 BMS Preliminary Design Complete
    BMS Preliminary Design completed for the 2nd part of board review. We will review the board and make changes before the board order date to hopefully prevent from ordering many different boards
2021-12-02 Continued Labeling Connectors and Pins
    Continued Labeling Connectors and Pins
2021-12-03 Fixing connector pin labels
    Fixing connector pin label positions and names to help clarify what each pin is
2021-12-09 Connector labels finished, and signature added
    Connector labels finished and signature added. Ready for a final check
2021-12-30 deleted excess files
    removed the 2019 bms that was used for reference from the project.
2021-12-30 deleted rescue libraries
2022-01-27 resize the board to 4.5*4.8 inch
2022-02-03 tracing
2022-02-03 Add some labels
2022-02-18 Recommiting from Onedrive issues
2022-02-20 Added mounting holes and created planes for V-in, V-out, and Pack_V
2022-02-22 placement of components
2022-02-22 add some tracing
2022-02-22 added some gnd vias
2022-03-05 Labeled connectors and moved components away from the edge of the board
2022-03-15 Fixed differential pairing and replaced the buck
2022-03-15 Updated component properly, and changed power traces
2022-03-19 Added drill holes, edge cutts, fixed traces created Gerbs
2022-03-20 fix diff pair on ethernet, gerbs
    pins 1&2 on the ethernet connectors are now 0.2 mil difference
2022-08-27 repo organization and TINA simulation uploaded
2022-09-14 BMS layout complete pending ethernet circuit and review
2022-09-15 Revised/Copied 2022REV3
2022-09-15 Revert "project files added"
    This reverts commit 8086f0852cdfb2e6128b82a6a5fbb46ff01e7da6.
2022-09-16 Laid out opamps, began current sense circuitry
2022-09-19 Current sense add-ons
2022-09-19 Revert "Began Footprinting"
    This reverts commit 0adb7fbdf8f9c66542aacd43b251b4210336c121.
2022-09-20 For safety
2022-09-22 no changes
2022-09-22 Removed other Kicad Projects
    Yo pull up these other repos by swapping branches, its super jank having like 4 kicad projects in one branch.
2022-09-22 Changed name of gitignore file to .gitignore
    I'm pretty sure it wasn't working before because it was named wrong.
2022-09-23 Prettied Up the Schematic
    1. Added blue borders and organized the function blocks.
    2. Swapped temp sensor back to using 3V3 source, not sure if powering with 5V will make the output data voltage too large for teensy.
2022-09-30 Labeling changes
    Added labels to voltage sense conns
2022-09-30 Rearranged Components to fit new page size
2022-10-01 Adding PDF
    PDF for PDR
2022-10-01 Updated to BOM
2022-10-02 fixed stupid plot file
2022-10-04 Created new branch for new board
2022-10-04 fixed filesystem
2022-10-04 Prettied Ethernet Schmatic
2022-10-05 layout work
2022-10-06 pretty much did jack shit
2022-10-07 General board dimension
2022-10-07 started laying traces
2022-10-09 almost finished layout
    Still need larger diodes, and need to run pack out traces.
2022-10-11 Fixed fan circuit
    It's a 1x2 conn with power and ground now.
2022-10-11 Fan Schematic Rev3
    Eventually I'll learn how mosfets work...maybe.
2022-10-15 Put all power planes in layout
2022-10-20 forgot to save
2022-11-01 miscellaneous changes
2022-11-03 correct board dimensions and started redoing traces
2022-11-04 finished bms for board review
2022-11-05 Fixes from layout review
    Fixed rx diff pair
    Via stitched some power plains
    Big via spacing from edge
    Changed teensy 5v input to vin
    Fixed ground plane clearance
    Silk screen labels for LEDs
2022-11-10 replaced tht caps with smd
2022-11-11 Fixed vias and made pdf
2022-11-12 nothing major
2022-11-14 random push
2022-11-17 fixed edge cuts for Paul
2022-11-18 making documentation
2022-12-09 edits during soldering
2023-03-10 Added LEDs to MOSFETS and changed 1st batt pin next to gnd
2023-03-10 Finished schematic Rev2
2023-03-16 Dimensioned Rev2 Layout
2023-03-17 Layout of major components except opamps
2023-03-20 Completed Layout
2023-04-07 Idk what this is
2023-04-16 added drill origin
2023-04-16 updated to rev 2 schematic
2023-04-16 fixed mosfets on leds
2023-04-16 updated to match 2023rev2
2023-04-16 Updated to where rev 2 is
2023-04-18 started adding caps
2023-04-21 Added caps for all cells
2023-09-04 added in molex
2023-09-27 Updated rev1
2023-09-28 changes from schematic review
2023-10-01 finished schematic after PDR
2023-10-08 worked on board connections
2023-10-11 polished components placement
2023-10-12 final component arrangement
2023-10-13 enlarged board and pack zones
2023-10-16 Added Signature
2023-10-19 did more traces
2023-10-20 rearranged flags and labeled LED
2023-10-26 did secondary review changes
2023-11-01 added in mars rover logo and gnd via label
